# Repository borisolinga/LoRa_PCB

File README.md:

# LoRa-Sender PCB

Die Leiterplatte (PCB) des LoRa-Senders deckt alle für dieses Projekt erforderlichen Funktionen ab. Das Design des Schaltplans und der Platinenlayouts wurde mit der EDA-Software (Electronic Design Automation) **Autodesk EAGLE** entwickelt.

## Eigenschaften der Leiterplatte

Die Leiterplatte bietet folgende Hauptfunktionen:

- **LoRa-Datenübertragung:** Das Board ermöglicht eine zuverlässige Kommunikation über LoRa.
- **Status-LED:** Eine LED zeigt durch Blinken an, wenn ein Paket erfolgreich gesendet wurde.
- **Serielle Schnittstelle:** Eine UART/USB-Schnittstelle ermöglicht die Kommunikation mit einem Computer.
- **Mikrocontroller:**  
  - **ATmega328P**, der aufgrund seiner Kompatibilität mit Arduino-Entwicklungsboards ausgewählt wurde.  
 
- **Stromverbrauchsmessung:**  
  - Zwei Jumper sind zur Stromverbrauchsanalyse vorgesehen:  
    1. Für das LoRa-Modul.  
    2. Für das Gesamtsystem.
  - Ein zusätzlicher Jumper ermöglicht die Nutzung einer externen Stromversorgung.

## Projektinhalt

- **Schaltplan:** Enthält das vollständige PCB-Design in Autodesk EAGLE.
- **Stückliste (BOM):** Eine vollständige Liste der verwendeten Komponenten.

## Nutzung

1. **Repository klonen:**

   ```bash
   git clone https://github.com/borisolinga/LoRa_Transmitter_PCB.git
   cd LoRa_Transmitter_PCB

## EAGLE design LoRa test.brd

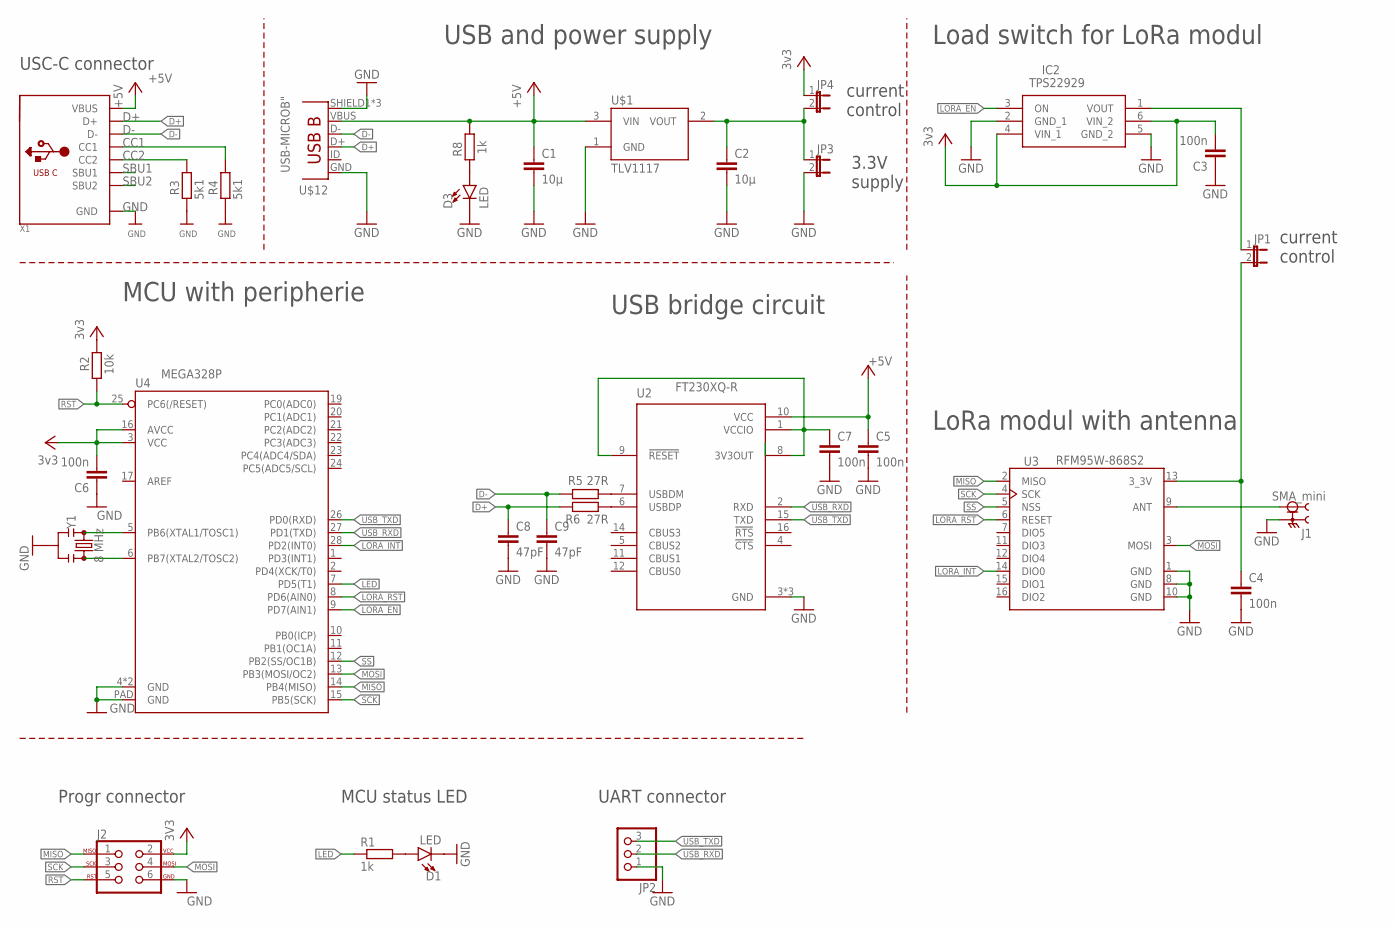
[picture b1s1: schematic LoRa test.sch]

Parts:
C1, C2: 10µ; C1206K
C3, C4, C5, C6, C7: 100n; C0603
C8, C9: 47pF; C0603
D1, D3: LED; LED-0603
IC2: TPS22929; SOP95P280X145-6N
J1: SMA_mini; LPRS_SMA_CONNECTOR
J2: AVR_SPI_PROG_3X2NS; 2X3-NS
JP1, JP3, JP4: JP1E; JP1
JP2: PINHD-1X3; 1X03
R1, R8: 1k; R0603
R2: 10k; R0603
R3, R4: 5k1; R0603
R5, R6: 27R; R0603
U2: FT230XQ-R; QFN65P400X400X80-17N
U3: RFM95W-868S2; XCVR_RFM95W-868S2
U4: MEGA328P; VQFN-28
U$1: TLV1117; SOT223
U$12: USB-MICROB"; USB-B-MICRO-SMD_V03
X1: USB_C; USB_C_CUSB31-CFM2AX-01-X
Y1: 8 MHz; RESONATOR-SMD-3.2X1.3

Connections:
+5V: C1.1, C5.1, R8.1, U2.10 (VCC), U$1.3 (VIN), U$12.VBUS, X1.A4B9 (VBUS), X1.B4A9 (VBUS)
CC1: R4.1, X1.A5 (CC1)
CC2: R3.1, X1.B5 (CC2)
D+: C8.1, R6.2, U$12.D+, X1.A6 (D+), X1.B6 (D+)
D-: C9.1, R5.2, U$12.D-, X1.A7 (D-), X1.B7 (D-)
GND: C1.2, C2.2, C3.1, C4.2, C5.2, C6.1, C7.2, C8.2, C9.2, D1.C, D3.C, IC2.2 (GND_1), IC2.5 (GND_2), J1.G1 (2), J1.G2 (2), J1.G3 (2), J1.G4 (2), J2.6, JP2.1, JP3.2, R3.2, R4.2, U2.3 (GND), U2.13 (GND), U2.17 (GND), U3.1 (GND), U3.8 (GND), U3.10 (GND), U4.4 (GND), U4.18 (GND), U4.PAD (GND), U$1.1 (GND), U$12.GND, U$12.SHIELD1 (SHIELD), U$12.SHIELD2 (SHIELD), U$12.SHIELD3 (SHIELD), X1.A1B12 (GND), X1.B1A12 (GND), Y1.2
LED: R1.1, U4.7 (PD5(T1))
LORA_EN: IC2.3 (ON), U4.9 (PD7(AIN1))
LORA_INT: U3.14 (DIO0), U4.28 (PD2(INT0))
LORA_RST: U3.6 (RESET), U4.8 (PD6(AIN0))
MISO: J2.1, U3.2 (MISO), U4.14 (PB4(MISO))
MOSI: J2.4, U3.3 (MOSI), U4.13 (PB3(MOSI/OC2))
unnamed: D1.A, R1.2
unnamed: J1.1, U3.9 (ANT)
unnamed: R5.1, U2.7 (USBDM)
unnamed: IC2.1 (VOUT), JP1.1
unnamed: D3.A, R8.2
unnamed: R6.1, U2.6 (USBDP)
unnamed: C7.1, U2.1 (VCCIO), U2.8 (3V3OUT), U2.9 (!RESET!)
unnamed: U4.5 (PB6(XTAL1/TOSC1)), Y1.1
unnamed: U4.6 (PB7(XTAL2/TOSC2)), Y1.3
unnamed: C2.1, JP3.1, JP4.2, U$1.2 (VOUT), U$1.4 (VOUT2)
unnamed: C4.1, JP1.2, U3.13 (3_3V)
RST: J2.5, R2.2, U4.25 (PC6(/RESET))
SBU1: X1.A8 (SBU1)
SBU2: X1.B8 (SBU2)
SCK: J2.3, U3.4 (SCK), U4.15 (PB5(SCK))
SS: U3.5 (NSS), U4.12 (PB2(SS/OC1B))
USB_RXD: JP2.2, U2.2 (RXD), U4.27 (PD1(TXD))
USB_TXD: JP2.3, U2.15 (TXD), U4.26 (PD0(RXD))
VCC: C3.2, C6.2, IC2.4 (VIN_1), IC2.6 (VIN_2), J2.2, JP4.1, R2.1, U4.3 (VCC), U4.16 (AVCC)

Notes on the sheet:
USB and power supply
Load switch for LoRa modul
USB bridge circuit
LoRa modul with antenna
current control
3.3V supply
MCU with peripherie
MCU status LED
Progr connector
USC-C connector
UART connector

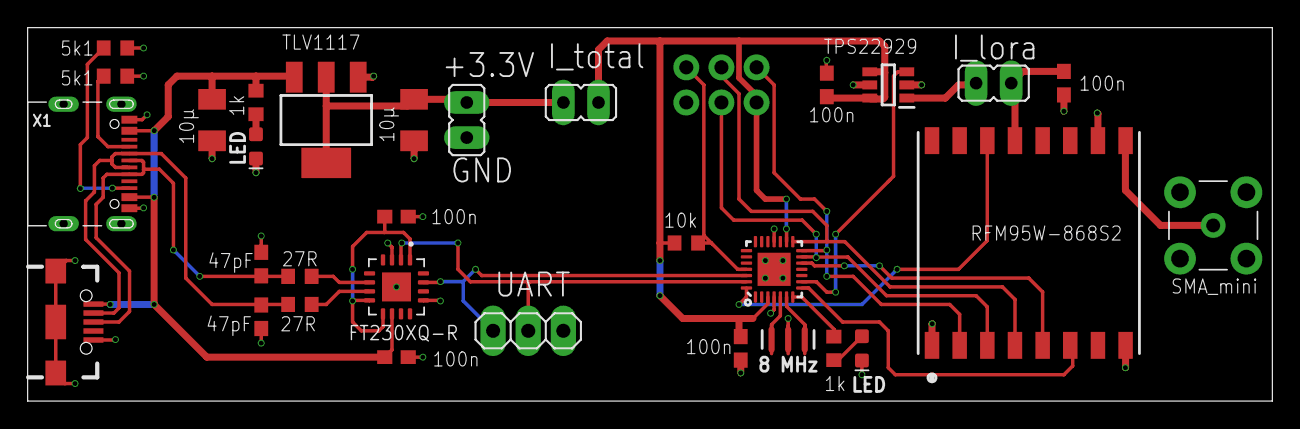
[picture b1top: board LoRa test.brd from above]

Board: 2 copper layers, 90.0 x 27.0 mm, 32 parts (0 on the bottom side), 29 nets.

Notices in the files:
parts and their libraries:
SparkFun-LED: Licensing: Creative Commons ShareAlike 4.0 International - https://creativecommons.org/licenses/by-sa/4.0
microbuilder: This work is placed in the public domain, and may be freely used for commercial and non-commercial work with the following conditions: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
